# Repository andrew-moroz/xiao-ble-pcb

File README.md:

# xiao-ble-pcb

A simple example Eagle project for the <a href="https://github.com/meshtastic/firmware/pull/2633" target="_blank">Xiao BLE + E22-900M30S Meshtastic variant</a>.

#### UPDATE:
The first round of boards was delivered yesterday (7/25/23) and work well, with two small caveats:
* I'm an idiot and reversed MISO and MOSI, which fortunately can be fixed easily by swapping the pin mappings for those two in the firmware (`variant.h:98-99`).

* The landing pads for the MiniBoost were just a little too close to the XIAO for it to fit. I worked around this by scooting the XIAO up a tiny bit on its pads, which created enough overlap between the MiniBoost's landing pads and its through holes for it to be soldered on.

I revised the board to fix these issues and also added another four-pin breakout to expose the XIAO's underside RST, GND, SWDIO, and SWCLK pins. The RST and GND pins can be used to add a secondary external reset switch, which is handy since the built-in reset button on the XIAO is not particularly easy to access once it's in an enclosure.

#### This new version of the board is currently untested, so it's still "build at your own risk" for the time being. I'll post another update once I receive them, probably mid-August 2023.

&nbsp;
---
&nbsp;

This PCB is set up to use the E22 in 'automatic Tx/Rx switching' mode, with TXEN and DIO2 connected to each other rather than to the Xiao. I created it with two additional breakout boards in mind – the <a href="https://www.adafruit.com/product/1863" target="_blank">Adafruit Switched JST Breakout</a> and the <a href="https://www.adafruit.com/product/4654" target="_blank">Adafruit MiniBoost</a>. The switched JST goes in the GND, SW, +, and GND pins, and the MiniBoost goes in the EN, 5V, GND, and VIN pins. You can of course use any other 5V power source, and/or forego the JST board and solder the battery directly to the board, but the breakouts are inexpensive ($6.50 USD before tax and shipping) and ideally suited to the task. 

To get the full 30 dBm transmit power out of the E22, a buffering capacitor (ideally at least 100 µF) should be placed between the 5V rail and GND. If using the MiniBoost, you can place a through-hole capacitor across its 5V and GND pins and then use the cap's leads in place of header pins for those two pads. Alternately, you could solder a capacitor across pins 10 (VCC) and 11 (GND) on the E22.

The board breaks out the Xiao's unused GPIO pins (D4, D5, D6, NFC1, NFC2) and also preserves access to its SWCLK, SWDIO, RST, and GND pins on the bottom.

# Bill of materials

<strong>Note: </strong>You can use a Xiao BLE Sense instead if you want. I went with the non-sense version since it's $5 cheaper and I didn't need the extra bells and whistles.

| Part | Source | Cost&nbsp;(USD) | Note |
| :------------ | :---------------------------- | :-----------------| :-----------------|
| Xiao BLE | <a href="https://www.digikey.com/en/products/detail/seeed-technology-co-ltd/102010448/16652893" target="_blank">DigiKey</a> | $10.38 ||
| Ebyte E22-900M30S | <a href="https://www.aliexpress.us/item/3256801621928909.html" target="_blank">AliExpress</a> | $9.42 | Also available on <a href="https://www.amazon.com/EBYTE-E22-900M30S-Wireless-Transmitter-Receiver/dp/B07RLQ9LTF">Amazon</a> for a couple bucks more |
| Adafruit Switched JST Breakout | <a href="https://www.digikey.com/en/products/detail/adafruit-industries-llc/1863/6565368" target="_blank">DigiKey</a> | $2.50 ||
| Adafruit MiniBoost (5V @ 1A) | <a href="https://www.digikey.com/en/products/detail/adafruit-industries-llc/4654/12697636" target="_blank">DigiKey</a> | $3.95 ||
| 100 uF capacitor | <a href="https://www.digikey.com/en/products/detail/würth-elektronik/860040272001/5727432" target="_blank">DigiKey</a> | $0.13 | Just one example with decent specs, lots of other (and smaller) options available |
|&nbsp;&nbsp;&nbsp;&nbsp;&nbsp;&nbsp;&nbsp;&nbsp;&nbsp;&nbsp;&nbsp;&nbsp;&nbsp;&nbsp;&nbsp;&nbsp;&nbsp;&nbsp;&nbsp;&nbsp;&nbsp;&nbsp;&nbsp;&nbsp;&nbsp;&nbsp;&nbsp;&nbsp;&nbsp;&nbsp;&nbsp;&nbsp;&nbsp;&nbsp;&nbsp;&nbsp;&nbsp;&nbsp;&nbsp;&nbsp;&nbsp;&nbsp;&nbsp;&nbsp;&nbsp;&nbsp;&nbsp;&nbsp;&nbsp;&nbsp;&nbsp;&nbsp;&nbsp;&nbsp;&nbsp;&nbsp;||||
| <strong>Total</strong> || $26.38 | Plus the cost of the PCB – roughly $25 (HASL w/ lead surface finish) or $55 (ENIG surface finish) for 10 boards at <a href="https://www.pcbway.com" target="_blank">pcbway.com</a>; can probably be had for less elsewhere |

# TODO

* Route the board manually
* Create a "version 2" for assembly with the boost converter, JST + switch, and maybe also a solar charge controller integrated into the design

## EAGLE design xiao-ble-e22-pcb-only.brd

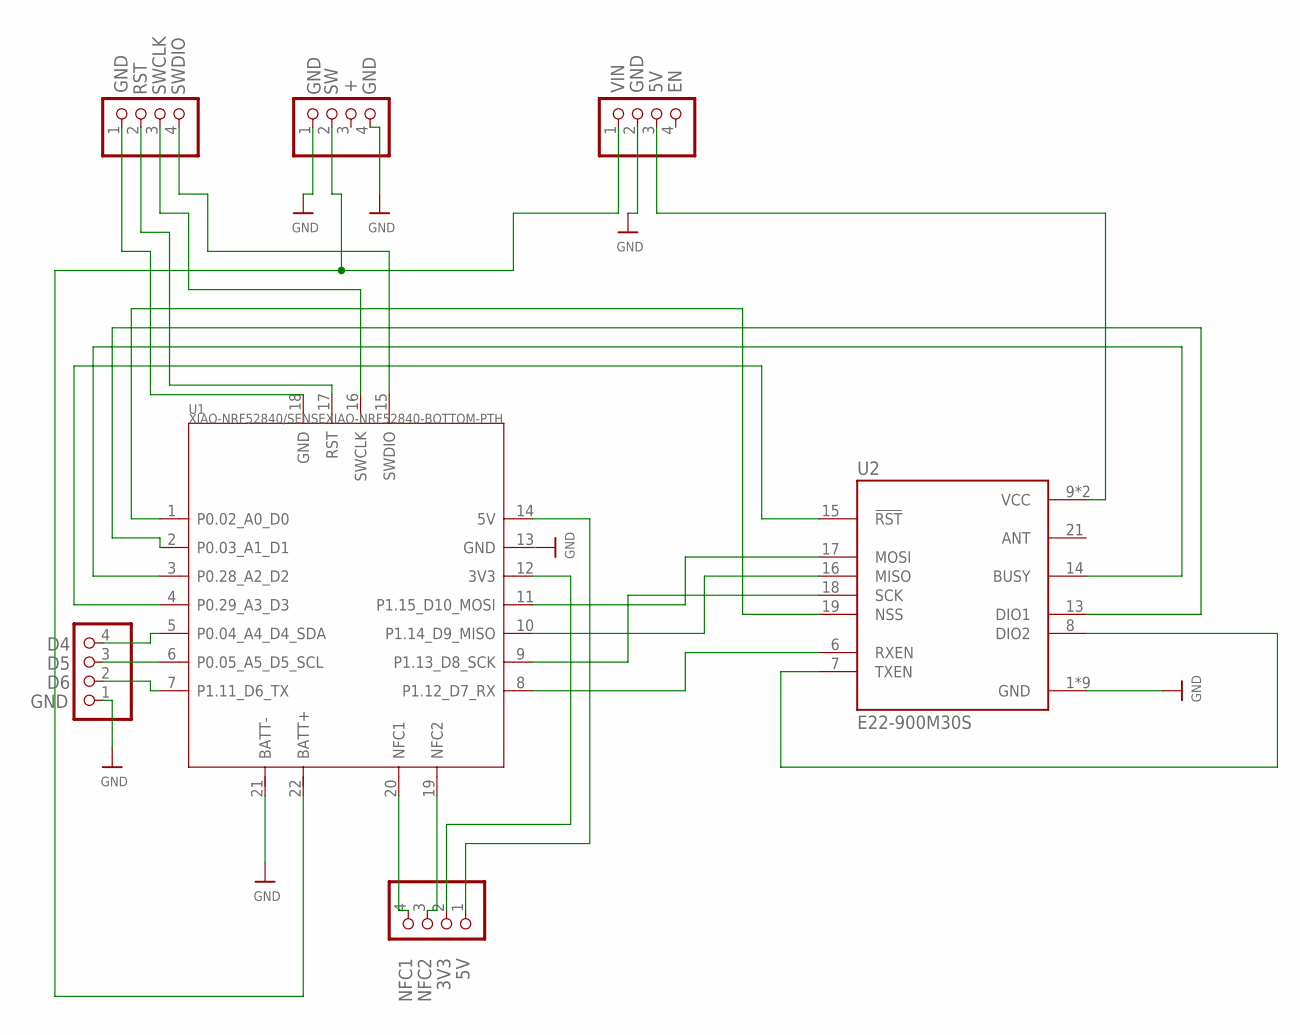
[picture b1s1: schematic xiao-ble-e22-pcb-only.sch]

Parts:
JP1: MiniBoost Breakout; PADS-4
JP2: GPIO Breakout 1; PADS-4
JP3, JP5: GPIO Breakout 2; PADS-4
JP4: JST + Switch Breakout; PADS-4
U1: XIAO-NRF52840/SENSEXIAO-NRF52840-BOTTOM-PTH; XIAO-NRF52840/SENSE-MODULE14P-2.54-21X17.8MM-BOTTOM-PTH
U2: E22-900M30S; XCVR_E22-900M30S

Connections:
GND: JP1.2, JP3.1, JP4.1, JP4.4, U1.13 (GND), U1.21 (BATT-), U2.1 (GND), U2.2 (GND), U2.3 (GND), U2.4 (GND), U2.5 (GND), U2.11 (GND), U2.12 (GND), U2.20 (GND), U2.22 (GND)
unnamed: JP1.3, U2.9 (VCC), U2.10 (VCC)
unnamed: JP2.4, U1.20 (NFC1)
unnamed: JP2.3, U1.19 (NFC2)
unnamed: U1.8 (P1.12_D7_RX), U2.6 (RXEN)
unnamed: U2.7 (TXEN), U2.8 (DIO2)
unnamed: U1.1 (P0.02_A0_D0), U2.19 (NSS)
unnamed: U1.9 (P1.13_D8_SCK), U2.18 (SCK)
unnamed: U1.10 (P1.14_D9_MISO), U2.16 (MISO)
unnamed: U1.11 (P1.15_D10_MOSI), U2.17 (MOSI)
unnamed: U1.2 (P0.03_A1_D1), U2.13 (DIO1)
unnamed: U1.3 (P0.28_A2_D2), U2.14 (BUSY)
unnamed: U1.4 (P0.29_A3_D3), U2.15 (!RST)
unnamed: JP1.1, JP4.2, U1.22 (BATT+)
unnamed: JP5.1, U1.18 (GND)
unnamed: JP2.1, U1.14 (5V)
unnamed: JP2.2, U1.12 (3V3)
unnamed: JP5.2, U1.17 (RST)
unnamed: JP3.4, U1.5 (P0.04_A4_D4_SDA)
unnamed: JP3.3, U1.6 (P0.05_A5_D5_SCL)
unnamed: JP3.2, U1.7 (P1.11_D6_TX)
unnamed: JP5.3, U1.16 (SWCLK)
unnamed: JP5.4, U1.15 (SWDIO)

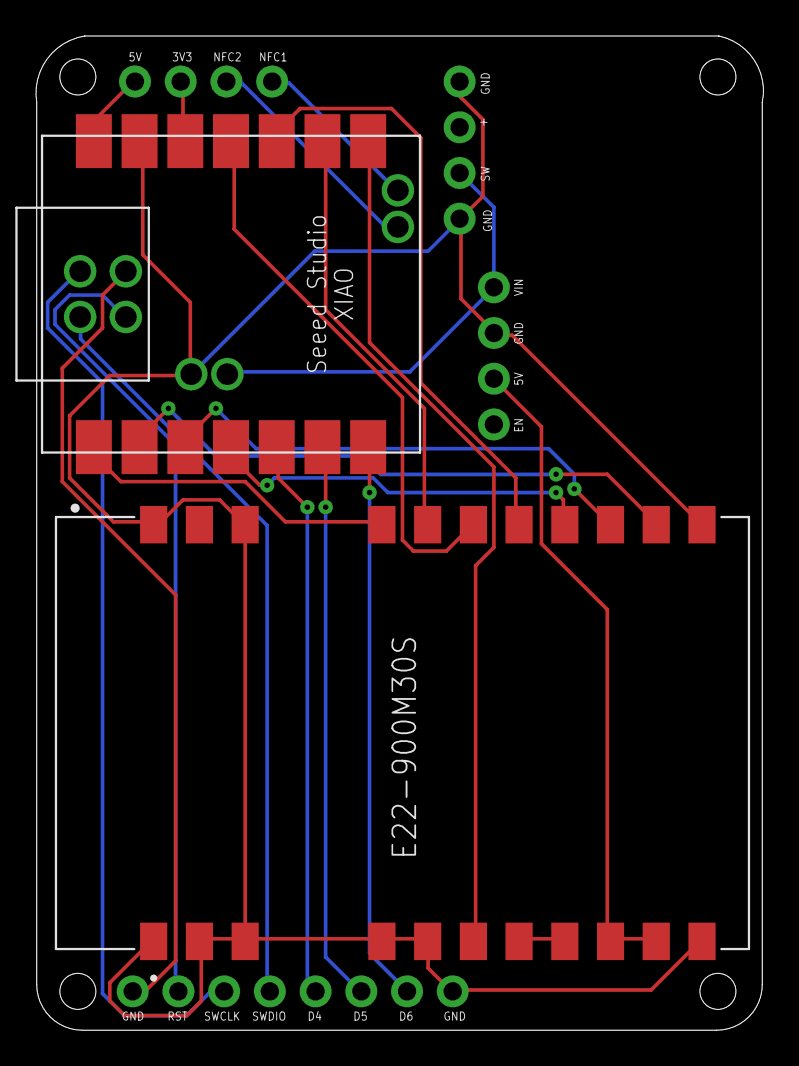
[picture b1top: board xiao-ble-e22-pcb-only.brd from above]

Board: 2 copper layers, 40.4 x 55.2 mm, 7 parts (0 on the bottom side), 23 nets.

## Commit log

2023-07-21 main: initial commit
2023-07-24 Add readme and gerbers
2023-07-26 Fix issues with board (spacing between XIAO and MiniBoost, MISO/MOSI swapperoo), break out debug pins, reroute

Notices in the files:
parts and their libraries:
microbuilder: This work is placed in the public domain, and may be freely used for commercial and non-commercial work with the following conditions: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
